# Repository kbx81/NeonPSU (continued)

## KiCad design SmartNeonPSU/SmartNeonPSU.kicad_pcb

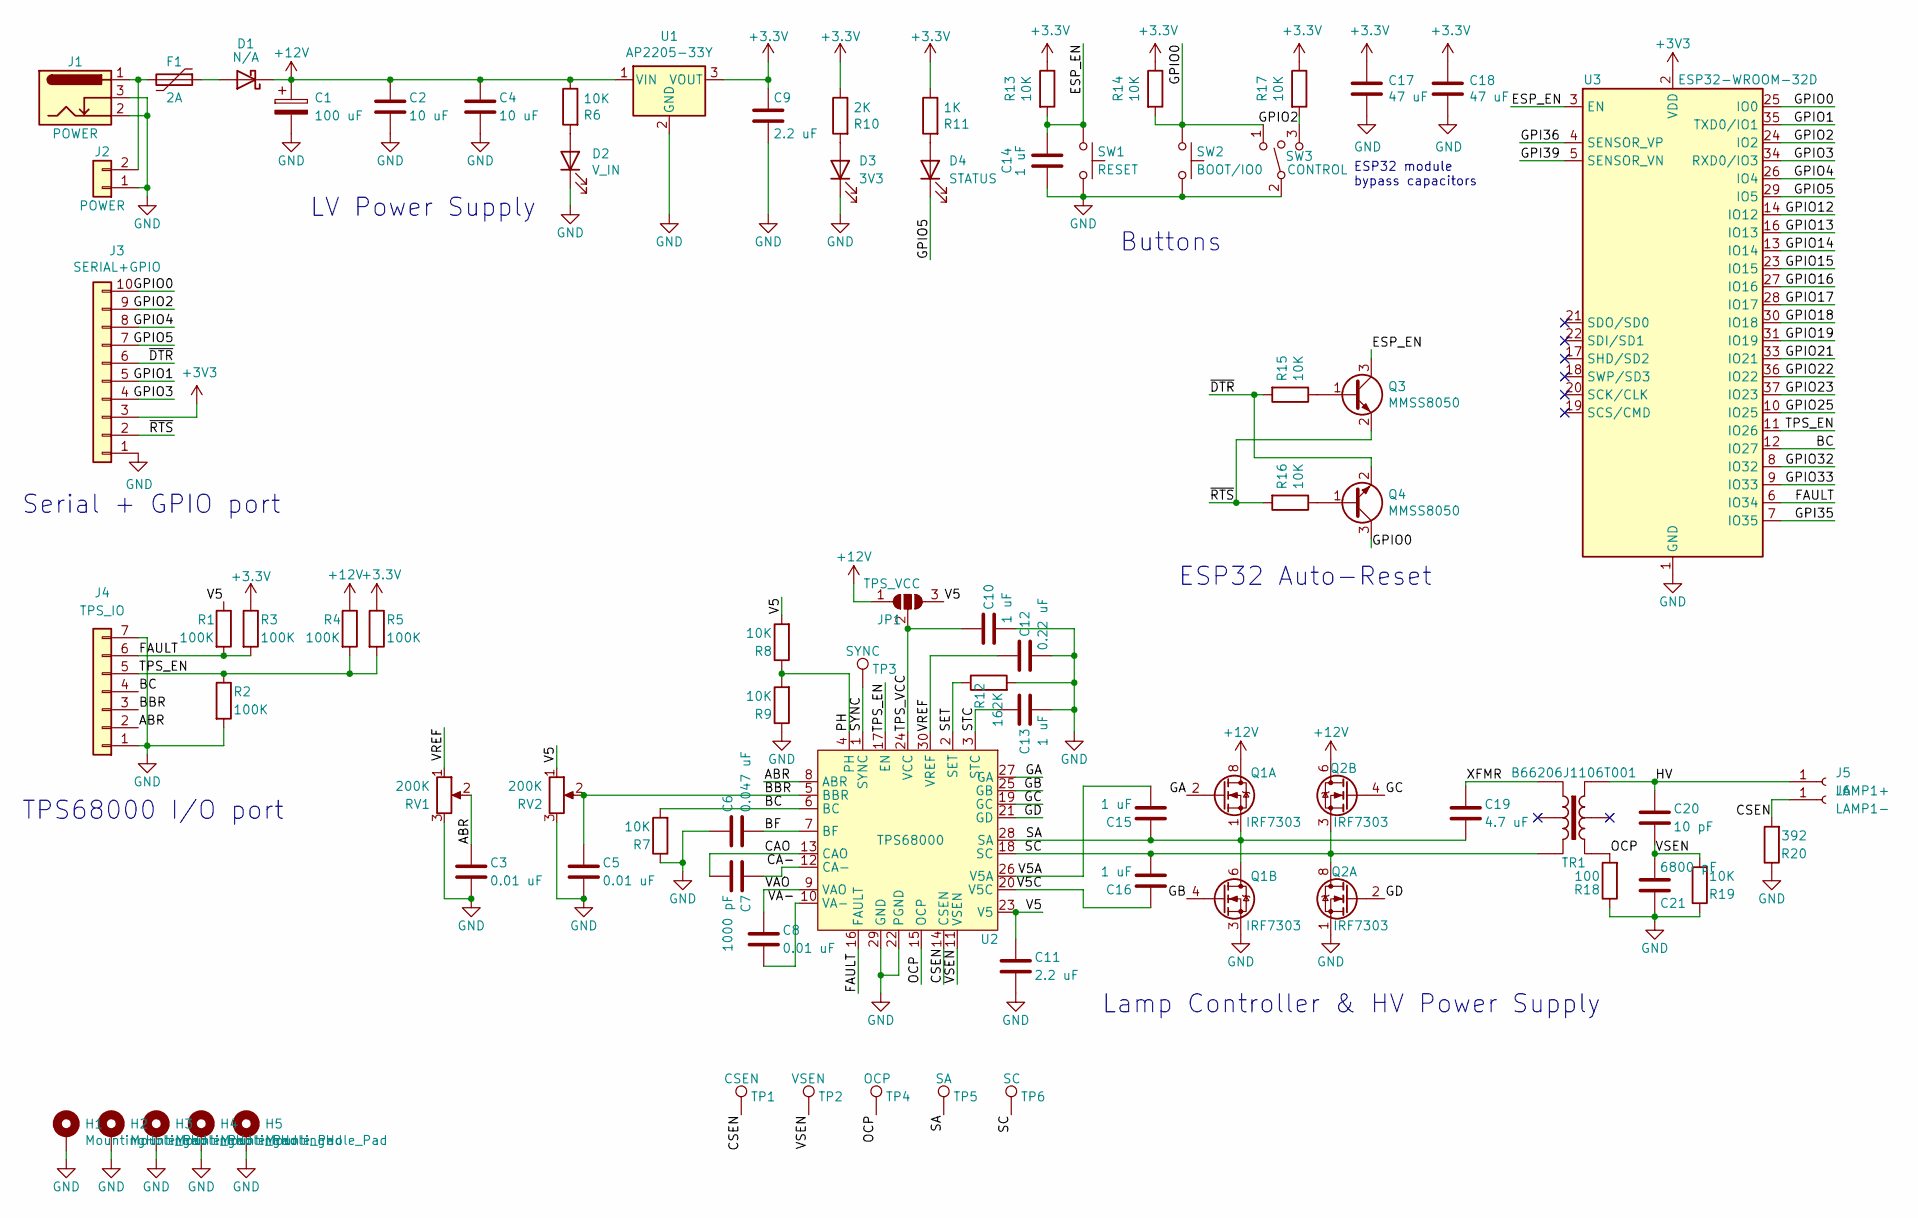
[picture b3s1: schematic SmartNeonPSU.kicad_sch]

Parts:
C1: 100 uF; CP_Elec_5x5.3; MPN1 25SVF100M
C2, C4: 10 uF; C_0805_2012Metric; MPN1 C2012X5R1V106K085AC
C3, C5, C8: 0.01 uF; C_0805_2012Metric; MPN1 CC0805JRX7R8BB103
C6: 0.047 uF; C_0805_2012Metric; MPN1 CC0805JRX7R9BB473
C7: 1000 pF; C_0805_2012Metric; MPN1 CC0805KRX7R9BB102
C9, C11: 2.2 uF; C_0805_2012Metric; MPN1 C2012X5R1E225M125AC
C10, C13, C14, C15, C16: 1 uF; C_0805_2012Metric; MPN1 C2012X5R1E105M125AA
C12: 0.22 uF; C_0805_2012Metric; MPN1 CC0805JRX7R7BB224
C17, C18: 47 uF; C_0805_2012Metric; MPN1 GRM21BR60J476ME15L
C19: 4.7 uF; C_0805_2012Metric; MPN1 C2012X7R1H475K125AE
C20: 10 pF; C_1808_4520Metric_Slot; MPN1 C4520C0G3F100F
C21: 6800 pF; C_0805_2012Metric; MPN1 CC0805KRX7R9BB682
D1: N/A; D_SOD-123F; MPN1 MBR230S1F-7
D2: V_IN; LED_0805_2012Metric; MPN1 LSM0805543V
D3: 3V3; LED_0805_2012Metric; MPN1 LSM0805543V
D4: STATUS; LED_0805_2012Metric; MPN1 APT2012EC
F1: 2A; Fuse_2920_7451Metric; MPN1 2920L030DR
H1, H2, H3, H4, H5: MountingHole_Pad; MountingHole_2.2mm_M2_Pad_Via
J1: POWER; BarrelJack_Horizontal
J2: POWER; PinSocket_1x02_P2.54mm_Vertical
J3: SERIAL+GPIO; PinSocket_1x10_P2.54mm_Vertical
J4: TPS_IO; PinSocket_1x07_P2.54mm_Vertical
J5: LAMP1+; SpringContact_9.9mm_5mm
J6: LAMP1-; SpringContact_9.9mm_5mm
JP1: TPS_VCC; SolderJumper-3_P1.3mm_Bridged12_RoundedPad1.0x1.5mm
Q1, Q2: IRF7303; SOIC-8_3.9x4.9mm_P1.27mm; MPN1 IRF7303TRPBF
Q3, Q4: MMSS8050; SOT-23; MPN1 MMSS8050
R1, R2, R3, R4, R5: 100K; R_0805_2012Metric; MPN1 RC0805FR-07100KL
R6, R7, R8, R9, R13, R14, R15, R16, R17, R19: 10K; R_0805_2012Metric; MPN1 RC0805FR-0710KL
R10: 2K; R_0805_2012Metric; MPN1 RC0805FR-072KL
R11: 1K; R_0805_2012Metric; MPN1 RC0805FR-071KL
R12: 162K; R_0805_2012Metric; MPN1 RC0805FR-07162KL
R18: 100; R_0805_2012Metric; MPN1 RC0805FR-07100RL
R20: 392; R_0805_2012Metric; MPN1 RC0805FR-07392RL
RV1, RV2: 200K; Potentiometer_Bourns_3266W_Vertical; MPN1 3266W-1-204LF
SW1: RESET; SW_Push_1P1T_NO_CK_KMR2; MPN1 KMR221GLFS
SW2: BOOT/IO0; SW_Push_1P1T_NO_CK_KMR2; MPN1 KMR221GLFS
SW3: CONTROL; E-Switch_R1966A‎_7mm_RA; MPN1 R1966IBLKBLKHR
TP1: CSEN; TestPoint_Pad_D1.0mm
TP2: VSEN; TestPoint_Pad_D1.0mm
TP3: SYNC; TestPoint_Pad_D1.0mm
TP4: OCP; TestPoint_Pad_D1.0mm
TP5: SA; TestPoint_Pad_D1.0mm
TP6: SC; TestPoint_Pad_D1.0mm
TR1: B66206J1106T001; MPN1 B66206J1106T001
U1: AP2205-33Y; SOT-89-3; MPN1 AP2205-33Y
U2: TPS68000; TSSOP-30_4.4x7.8mm_P0.5mm; MPN1 TPS68000DBT
U3: ESP32-WROOM-32D; ESP32-WROOM-32; MPN1 ESP32-WROOM-32D

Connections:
+12V: C1.1, C2.1, C4.1, D1.1 (K), JP1.1 (A), Q1.7 (D), Q1.8 (D), Q2.5 (D), Q2.6 (D), R4.1, R6.1, U1.1 (VIN)
/ABR: C3.1, J4.2, RV1.2, U2.8 (ABR)
/BBR: C5.1, J4.3, RV2.2, U2.5 (BBR)
/BC: J4.4, R7.2, U2.6 (BC), U3.12 (IO27)
/BF: C6.2, U2.7 (BF)
/CA-: C7.1, U2.12 (CA-)
/CAO: C7.2, U2.13 (CAO)
/CSEN: J6.1, R20.2, TP1.1, U2.14 (CSEN)
/ESP_EN: C14.1, Q3.3 (C), R13.2, SW1.1, U3.3 (EN)
/FAULT: J4.6, R1.2, R3.2, U2.16 (FAULT), U3.6 (IO34)
/GA: Q1.2 (G), U2.27 (GA)
/GB: Q1.4 (G), U2.25 (GB)
/GC: Q2.4 (G), U2.19 (GC)
/GD: Q2.2 (G), U2.21 (GD)
/GPI35: U3.7 (IO35)
/GPI36: U3.4 (SENSOR_VP)
/GPI39: U3.5 (SENSOR_VN)
/GPIO0: J3.10, Q4.3 (C), R14.2, SW2.1, SW3.1, U3.25 (IO0)
/GPIO1: J3.5, U3.35 (TXD0/IO1)
/GPIO2: J3.9, R17.2, SW3.3, U3.24 (IO2)
/GPIO3: J3.4, U3.34 (RXD0/IO3)
/GPIO4: J3.8, U3.26 (IO4)
/GPIO5: D4.1 (K), J3.7, U3.29 (IO5)
/GPIO12: U3.14 (IO12)
/GPIO13: U3.16 (IO13)
/GPIO14: U3.13 (IO14)
/GPIO15: U3.23 (IO15)
/GPIO16: U3.27 (IO16)
/GPIO17: U3.28 (IO17)
/GPIO18: U3.30 (IO18)
/GPIO19: U3.31 (IO19)
/GPIO21: U3.33 (IO21)
/GPIO22: U3.36 (IO22)
/GPIO23: U3.37 (IO23)
/GPIO25: U3.10 (IO25)
/GPIO32: U3.8 (IO32)
/GPIO33: U3.9 (IO33)
/HV: C20.1, J5.1, TR1.6
/OCP: R18.2, TP4.1, TR1.4, U2.15 (OCP)
/PH: R8.1, R9.2, U2.4 (PH)
/SA: C15.1, C19.2, Q1.1 (S), Q1.5 (D), Q1.6 (D), TP5.1, U2.28 (SA)
/SC: C16.2, Q2.3 (1), Q2.7 (D), Q2.8 (D), TP6.1, TR1.3, U2.18 (SC)
/SET: R12.1, U2.2 (SET)
/STC: C13.2, U2.3 (STC)
/SYNC: TP3.1, U2.1 (SYNC)
/TPS_EN: J4.5, R2.1, R4.2, R5.2, U2.17 (EN), U3.11 (IO26)
/TPS_VCC: C10.1, JP1.2 (C), U2.24 (VCC)
/V5: C11.1, JP1.3 (B), R1.1, R8.2, RV2.1, U2.23 (V5)
/V5A: C15.2, U2.26 (V5A)
/V5C: C16.1, U2.20 (V5C)
/VA-: C8.2, U2.10 (VA-)
/VAO: C8.1, U2.9 (VAO)
/VREF: C12.1, RV1.1, U2.30 (VREF)
/VSEN: C20.2, C21.1, R19.2, TP2.1, U2.11 (VSEN)
/XFMR: C19.1, TR1.1
/~DTR: J3.6, Q4.2 (E), R15.2
/~RTS: J3.2, Q3.2 (E), R16.2
GND: C1.2, C2.2, C3.2, C4.2, C5.2, C6.1, C9.2, C10.2, C11.2, C12.2, C13.1, C14.2, C17.2, C18.2, C21.2, D2.1 (K), D3.1 (K), H1.1, H2.1, H3.1, H4.1, H5.1, J1.2, J1.3, J2.1, J3.1, J4.1, J4.7, Q1.3 (1), Q2.1 (S), R2.2, R7.1, R9.1, R12.2, R18.1, R19.1, R20.1, RV1.3, RV2.3, SW1.2, SW2.2, SW3.2, U1.2 (GND), U2.22 (PGND), U2.29 (GND), U3.1 (GND), U3.15 (GND), U3.38 (GND), U3.39 (GND)
unnamed: D1.2 (A), F1.1
unnamed: D2.2 (A), R6.2
unnamed: D3.2 (A), R10.2
unnamed: D4.2 (A), R11.2
unnamed: F1.2, J1.1, J2.2
unnamed: Q3.1 (B), R15.1
unnamed: Q4.1 (B), R16.1

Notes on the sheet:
ESP32 module bypass capacitors
Lamp Controller & HV Power Supply
TPS68000 I/O port
Serial + GPIO port
ESP32 Auto-Reset
LV Power Supply
Buttons

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
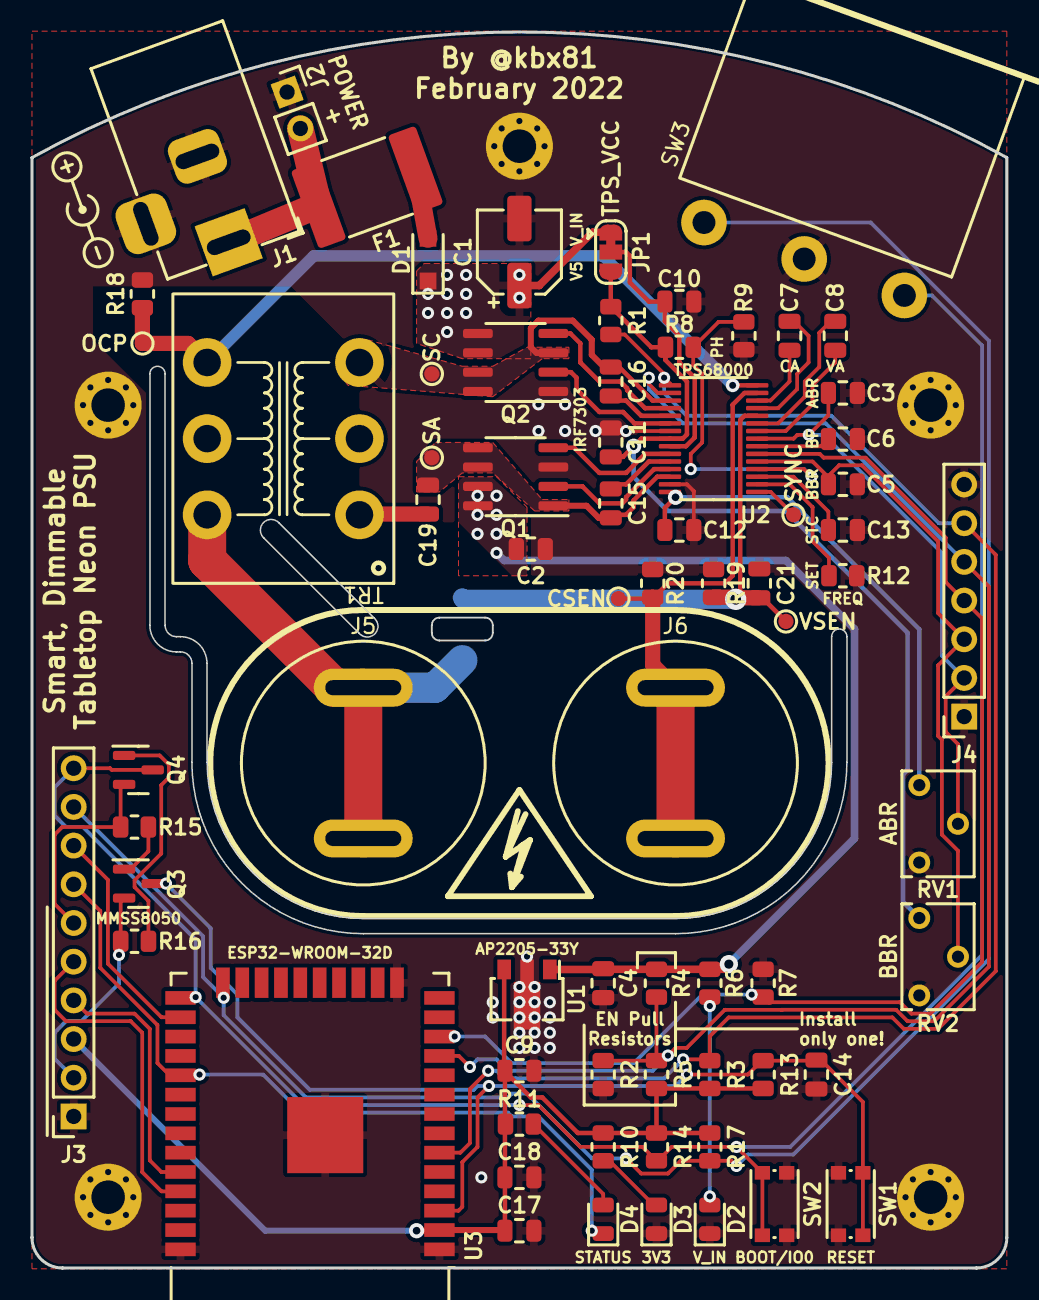
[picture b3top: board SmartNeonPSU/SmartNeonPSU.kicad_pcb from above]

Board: 2 copper layers, 64.0 x 81.1 mm, 77 parts (1 on the bottom side), 49 nets.

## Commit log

2022-03-02 Initial commit/v1
2022-05-01 Add docs, sync schematics with reality
2022-05-01 Copy tweaks
